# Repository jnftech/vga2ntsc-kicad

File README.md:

# RetroTINK VGA2NTSC - KiCad Conversion/Modification

This is a modified version of Mike Chi's VGA2NTSC v1.1.
The first goal was to convert the original Altium source files to KiCad - a free and open source tool - as not everyone has access to Altium. Secondly, most footprints have been swapped to make the board more DIY friendly - for example swapping 0402 components (difficult to solder by hand) with 0805 or larger.

As of April 2023, the version shown here is a "final" version (meaning I will no longer make further improvements) that I completed in mid-2021 and only now finally publishing to Github. The changes between the Old version (2020/04/20, archived in the "_Old" folder) and this version are outlined below. 

### Goals:
- Convert original Altium project to KiCad
- Use 0805 footprints instead of smaller packages
- Keep location of jacks and mounting holes in the same locations
- Keep circuit identical to original schematics
- Adjust vertical board size slightly to fit within 100x100mm size limit for cheap boards with many popular PCB fabs
- Add a footprint for a DC barrel jack instead of USB power (either-or can be used in the same spot). Warning has been added to the board denoting 5V power only
- Modified power distribution rail using bottom layer of board
- Relocated clock section to minimize routing near other signals or underneath video amp
- Minimized the use of vias for signal traces where possible.
- More KiCad practice for me
- Finally try to publish something on GitHub (first repo!)

### Changed from 2020/04/20 version:
- Tided up board outline and removed some workaround circular holes in some footprints.
- Added selectable HV/CSYNC switch
- AC coupling on the RGB lines of Scart Output (C22 - C25). The original design left these DC coupled. DC coupling can still be achieved by simply jumping the capacitor pads (for example using larger 0 ohm resistors, like 1206 or 1812)
- There are a few extra "tinkerer/advanced" pins (see below) but there are two solder jumpers implemented to make use of these.

### TL;DR on the two solder jumpers (JP1 and JP2)
- Close these both with solder if you want just NTSC video output. If you are not sure, then just close them both.

### Advanced/Tinkerer features (ignore this if you want just NTSC output with the standard board setup)
- Added a way to bypass the on-board clock circuit. This might be handy for someone wanting to get PAL output from the board by feeding in an external clock signal (EXT_CLOCK). See warning note below.
  - Note that JP1 must be closed with solder for "normal" NTSC operation using the onboard clock circuit. Leave JP1 open to feed external clock signal.
- Added pads for manipulating the NTSC/PAL pin on the AD725 if desired. Switching to PAL would require a different clock signal (see above, and see warning note below).
  - Close JP2 with solder for "normal" NTSC operation. (Just pulls the AD's STND pin high)
  - Leave JP2 open if you want the ability to toggle the mode.
  - WARNING: The three pins in the middle of the board (labeled "NTSC", "", and "PAL" on the underside) are there to implement a toggle. However the "NTSC" and "PAL" pins are just VCC and GND respectively, with the center pin being connected to the AD725's STND pin (which must be pulled either HIGH for NTSC, or LOW for PAL). As I did not have the foresight to think that through, there are no pullup/pulldown resistors. In other words DO NOT SHORT THE NTSC AND PAL PINS TOGETHER, and dont use MBB-style switches to toggle between.
- Added a YTRAP pad for feeding an external YTRAP circuit to the AD725.

### Notes:

<span style="color: red;">This board and circuit, as depicted in this repository, will only deliver an NTSC signal (hence the name VGA2NTSC).
Presence of the aforementioned extra pins (jumpers, clock and NTSC/PAL pins) do not indicate that this board natively supports PAL or any standard other than NTSC.
Those options are for advanced users/tinkerers that are prepard to supply the appropriate clock signal to the board to support other standards.</span>

The board design uses vias-in-pads. This can be a problem for some fabs. JLCPCB (at least with default HASL plating) and OSHpark dont seem to have an issue with this, but some fabs might depending on how they plate the pads. You may need to adjust the locations of the vias and add a couple traces to compensate, should you run into this situation.

### Tools used for conversion:
- Altium2Kicad https://github.com/thesourcerer8/altium2kicad
- Tracespace View (conversion of original Gerbers to SVG for reference and silkscreen adaptations - Alitum2Kicad doesn’t translate original fonts/graphics) https://tracespace.io/view/
- KiCad 5.1.8 https://www.kicad.org/
- Inkscape https://inkscape.org/

<p align="center">
<br />

<br />
</p>

This derivative work maintains the same source license as the original board.
https://www.retrotink.com/post/vga2ntsc-released

### “Mike Chi” License:
(From https://www.retrotink.com/post/vga2ntsc-released)

```
License
The materials are released under the terms below. I don't have time for pedantic nonsense or legal theory and like to keep things simple. I call this the 'Mike Chi' license.

- For each project, at my sole discretion, I may release whatever sources, to whatever level of abstraction, that I deem appropriate. Additional information/materials may be released on a scheduled determined at my sole discretion.
- You may modify, use or adapt any or all portions of the released material for any purpose you wish, including sale.
- The exception is that the files may not be used for commercial activities by entities, determined at my sole discretion, that have a history of violating intellectual property rights or licenses.
- If these materials were helpful and/or of use to you, I only ask that you provide some form of acknowledgment that you feel is fair.
- I'd also love to hear about how you're using it!
- If you re-distribute the material in a substantially unaltered form, please include this notice.
- NO WARRANTY EXPRESSED OR IMPLIED. WE TAKE ABSOLUTELY NO RESPONSIBILITY FOR WHAT MAY OCCUR FROM USAGE OF THE FILES.
- WE CANNOT AND WILL NOT OFFER ANY SUPPORT FOR THE USAGE OF THE FILES. IF YOU DO NOT AGREE WITH THESE TERMS THEN DO NOT USE ANY OF THE MATERIALS AND DON'T COMPLAIN.
```

https://www.retrotink.com/

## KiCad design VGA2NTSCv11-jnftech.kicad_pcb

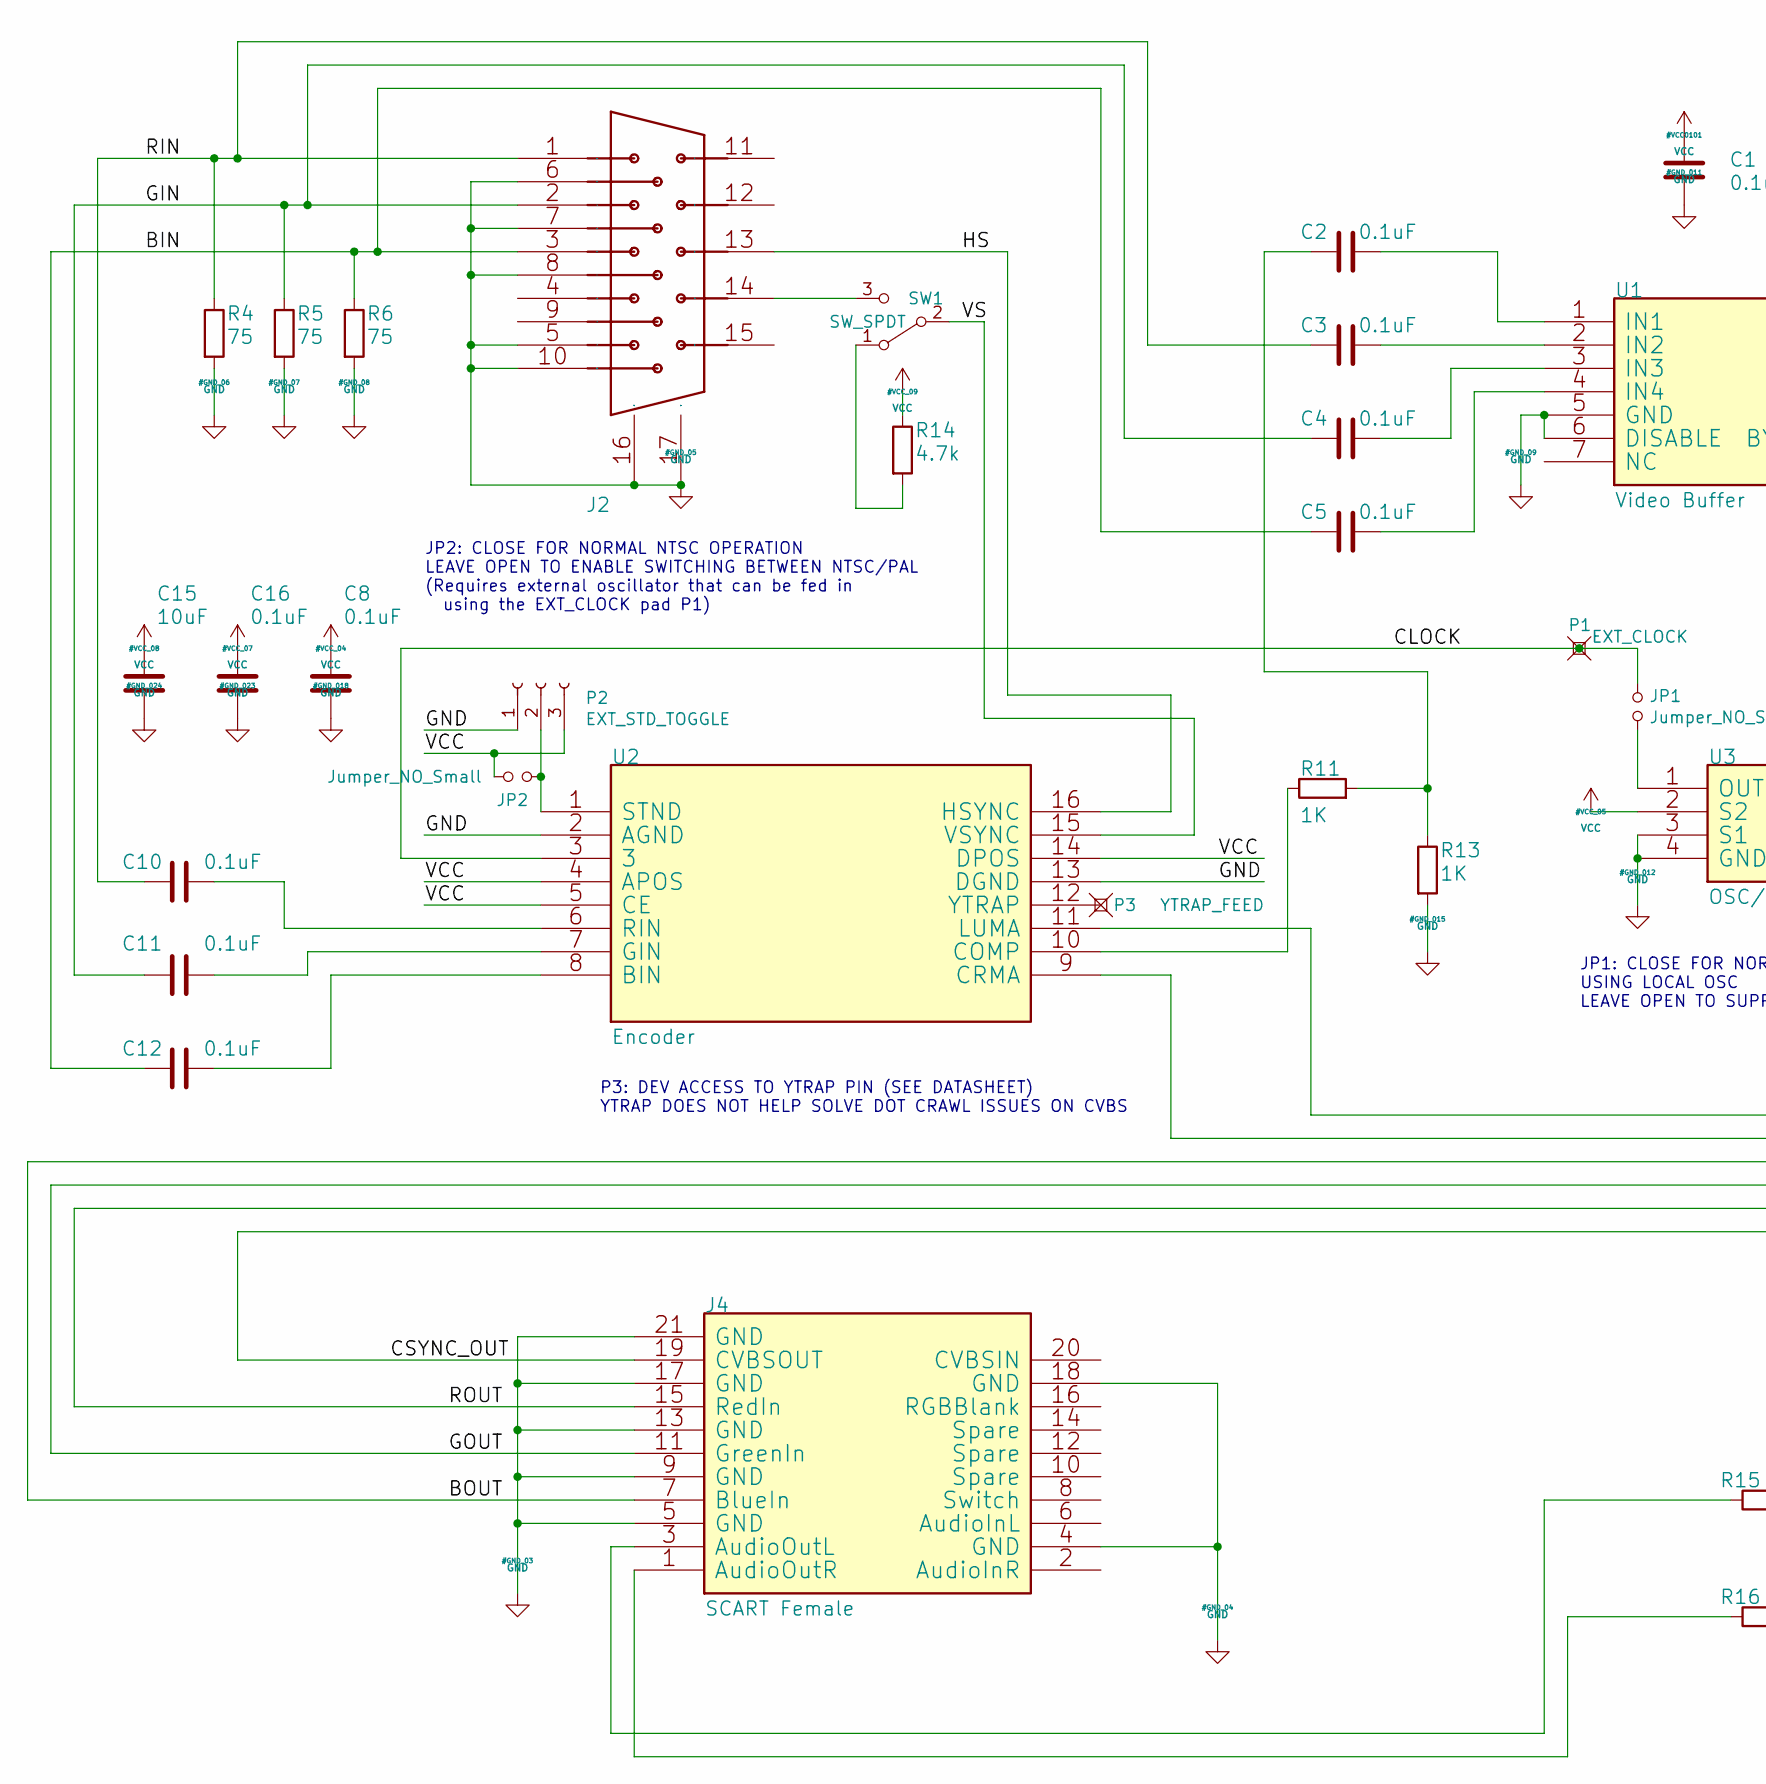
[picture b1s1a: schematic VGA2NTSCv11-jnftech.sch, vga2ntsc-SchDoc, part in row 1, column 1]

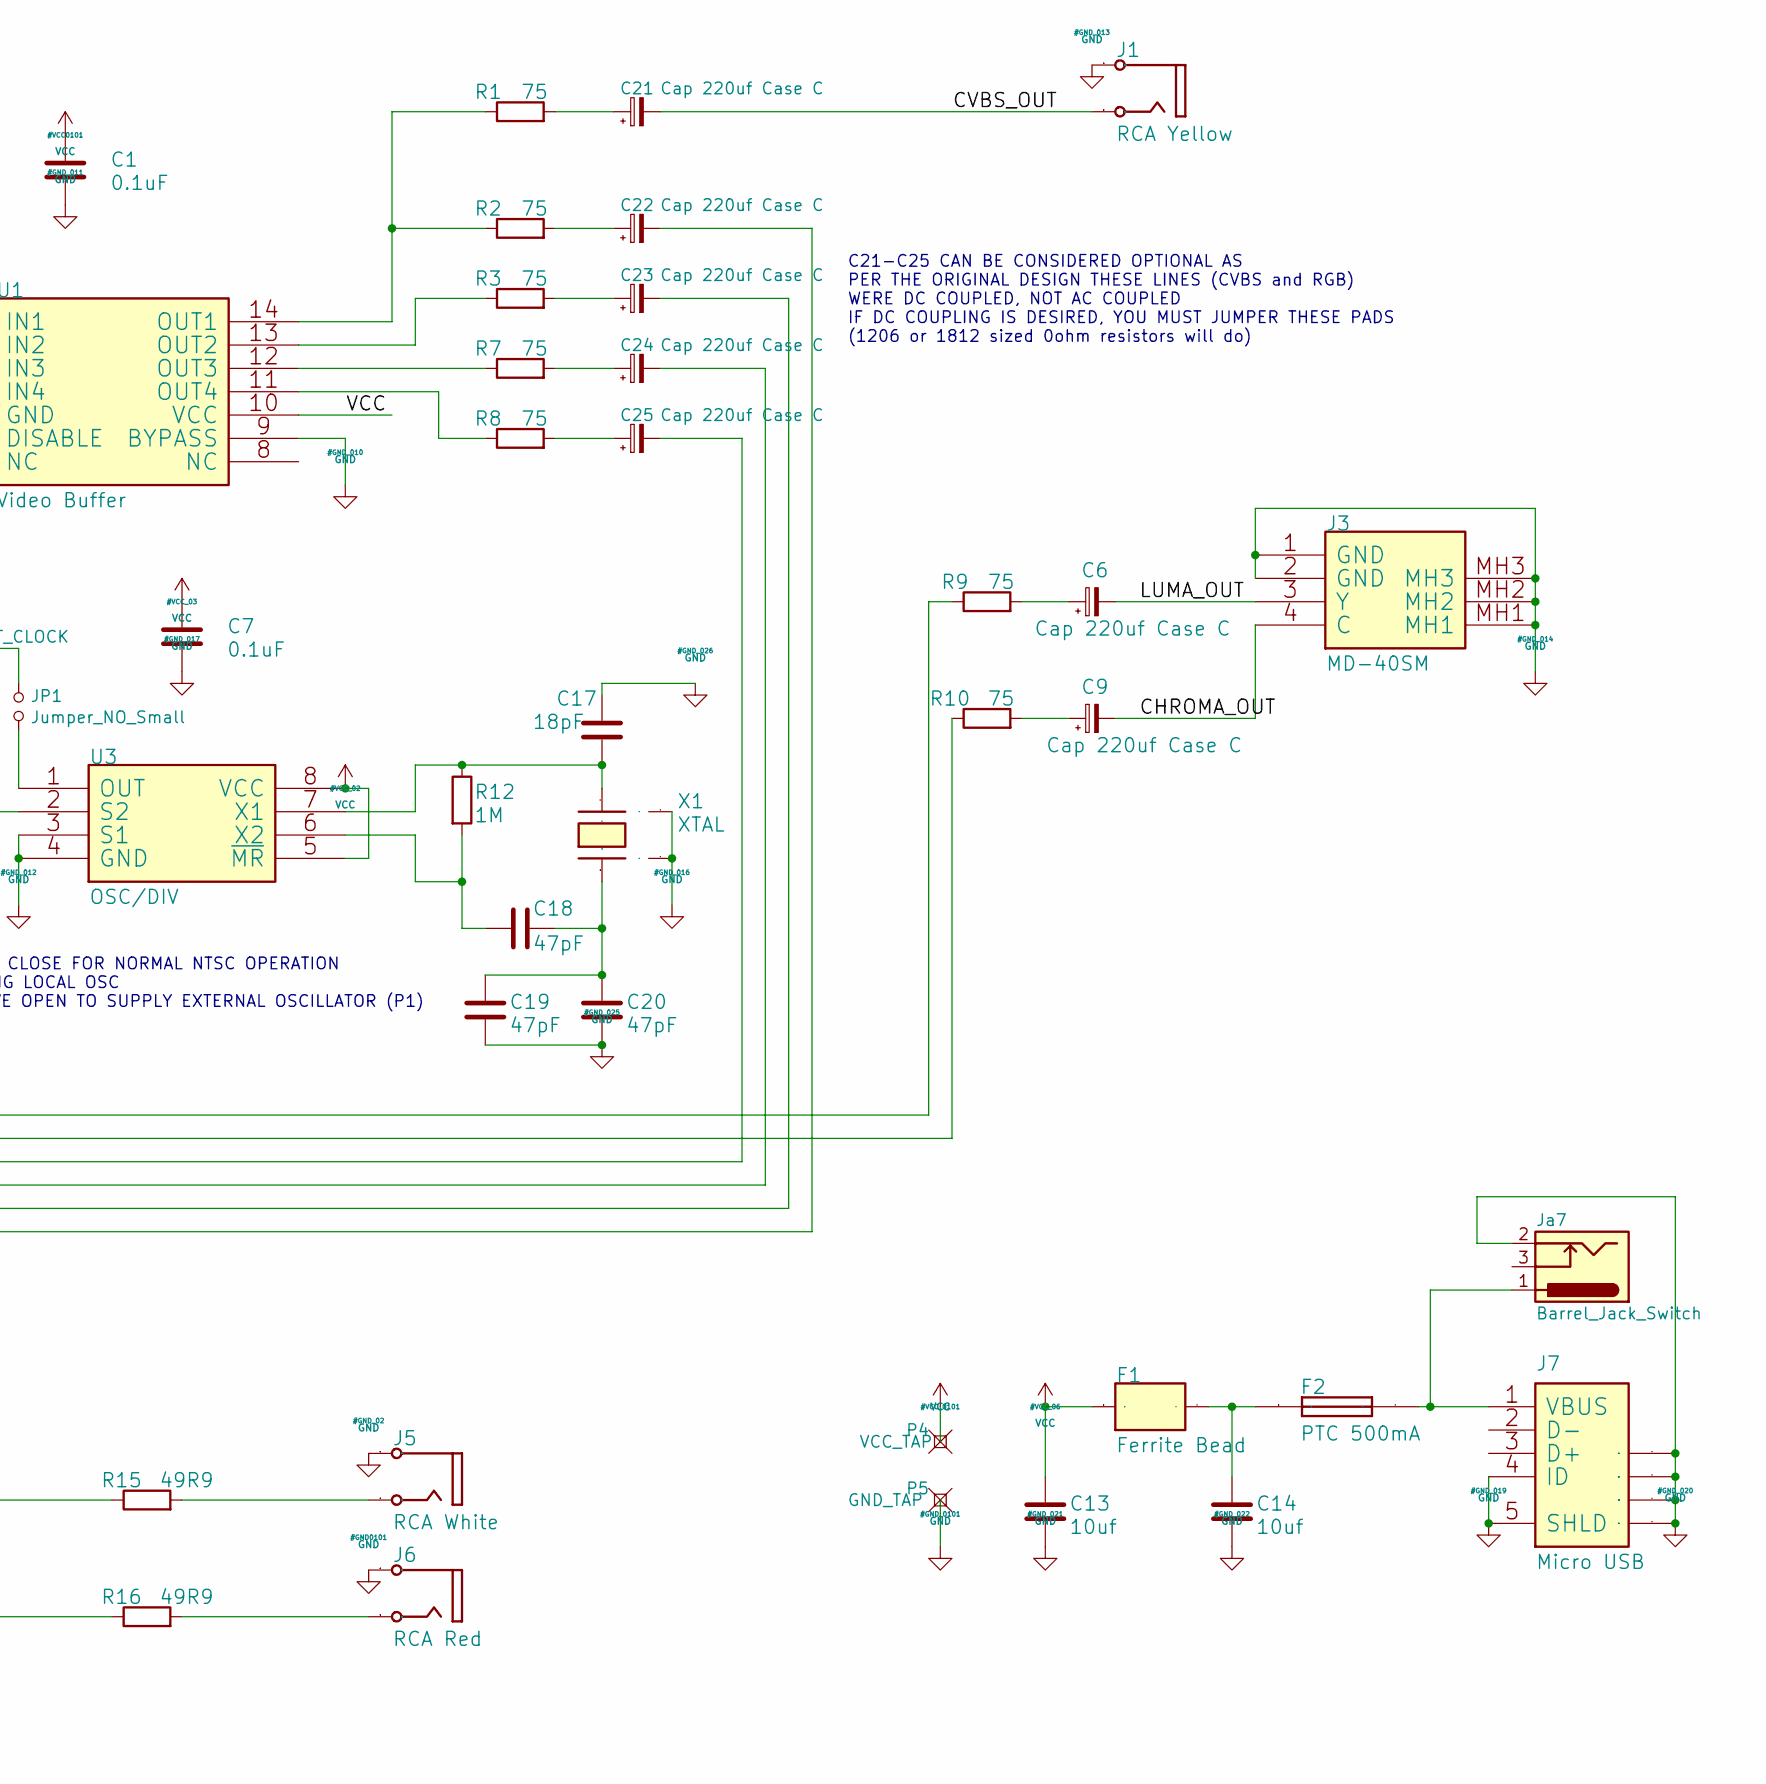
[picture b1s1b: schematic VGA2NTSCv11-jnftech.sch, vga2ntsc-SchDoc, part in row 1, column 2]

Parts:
C1, C2, C3, C4, C5, C7, C8, C10, C11, C12, C16: 0.1uF; R_0805_1mm
C6, C9, C21, C22, C23, C24, C25: Cap 220uf Case C; CP_Tantalum_Case-C_EIA-6032-28_JFT
C13, C14: 10uf; R_0805_1mm
C15: 10uF; R_0805_1mm
C17: 18pF; R_0805_1mm
C18, C19, C20: 47pF; R_0805_1mm
F1: Ferrite Bead; R_0805_1mm
F2: PTC 500mA; R_1812_1206-JFT
J1: RCA Yellow; RCJ-04x_NoHole
J2: AMPHENOL_L77HDE15SD1CH4F_Drill1SizeOval
J3: MD-40SM; CUI_MD-40SM_VGA2NTSC
J4: SCART Female; SCART-F-RA-NoHole
J5: RCA White; RCJ-04x_NoHole
J6: RCA Red; RCJ-04x_NoHole
J7: Micro USB; Connector_MicroUSB_Amp10118194-0001LF
JP1, JP2: Jumper_NO_Small; WirepadJumperSm
Ja7: Barrel_Jack_Switch; BARREL_JACK-JFT
P1: EXT_CLOCK; TH_Hole_One_1mm
P2: EXT_STD_TOGGLE; Pin_Header_Straight_1x03_Pitch2.54mm_NoSilk
P3: YTRAP_FEED; TH_Hole_One_1mm
P4: VCC_TAP; TH_Hole_One_1mm
P5: GND_TAP; TH_Hole_One_1mm
R1, R2, R3, R7, R8, R9, R10: 75; R_0805_1mm
R4, R5, R6: 75; R_0805_1mm; Tolerance 1%
R11, R13: 1K; R_0805_1mm; Tolerance 1%
R12: 1M; R_0805_1mm; Tolerance 1%
R14: 4.7k; R_0805_1mm; Tolerance 5%
R15, R16: 49R9; R_0805_1mm
SW1: SW_SPDT; SW_HRO-SK-12D02_SPDT_Angled
U1: Video Buffer; TSSOP-14_4.4x5mm_Pitch0.65mm-JFT
U2: Encoder; SOIC-16W_7.5x10.3mm_Pitch1.27mm_HS
U3: OSC/DIV; SOIC-8_3.9x4.9mm_Pitch1.27mm-JFT
X1: XTAL; Crystal_4SMD-NL_3.2mmx2.5mm_HandSolder

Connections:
/BIN: C5.1, C12.1, J2.3, R6.1
/BOUT: C25.2, J4.7 (BlueIn)
/CHROMA_OUT: C9.2, J3.4 (C)
/CLOCK: JP1.1, P1.1, U2.3
/CSYNC_OUT: C22.2, J4.19 (CVBSOUT)
/CVBS_OUT: C21.2, J1.2B (Signal)
/GIN: C4.1, C11.1, J2.2, R5.1
/GOUT: C24.2, J4.11 (GreenIn)
/HS: J2.13, U2.16 (HSYNC)
/LUMA_OUT: C6.2, J3.3 (Y)
/RIN: C3.1, C10.1, J2.1, R4.1
/ROUT: C23.2, J4.15 (RedIn)
/VS: SW1.2 (B), U2.15 (VSYNC)
GND: C1.1, C7.1, C8.1, C13.2, C14.2, C15.2, C16.1, C17.1, C19.1, C20.1, J1.1A (Ground), J2.5, J2.6, J2.7, J2.8, J2.10, J2.16, J2.17, J3.1 (GND), J3.2 (GND), J3.MH1, J3.MH2, J3.MH3, J4.4 (GND), J4.5 (GND), J4.9 (GND), J4.13 (GND), J4.17 (GND), J4.18 (GND), J4.21 (GND), J5.1A (Ground), J6.1A (Ground), J7.4 (ID), J7.5 (SHLD), J7.6 (SHLD), J7.7 (SHLD), J7.8 (SHLD), J7.9 (SHLD), Ja7.2, P2.1, P5.1, R4.2, R5.2, R6.2, R13.2, U1.5 (GND), U1.6 (DISABLE), U1.9 (BYPASS), U2.2 (AGND), U2.13 (DGND), U3.3 (S1), U3.4 (GND), X1.2, X1.4
unnamed: C2.1, R11.2, R13.1
unnamed: C2.2, U1.1 (IN1)
unnamed: C3.2, U1.2 (IN2)
unnamed: C4.2, U1.3 (IN3)
unnamed: C5.2, U1.4 (IN4)
unnamed: C6.1, R9.2
unnamed: C9.1, R10.2
unnamed: C10.2, U2.6 (RIN)
unnamed: C11.2, U2.7 (GIN)
unnamed: C12.2, U2.8 (BIN)
unnamed: C14.1, F1.2, F2.1
unnamed: C17.2, R12.1, U3.7 (X1), X1.3
unnamed: C18.1, R12.2, U3.6 (X2)
unnamed: C18.2, C19.2, C20.2, X1.1
unnamed: C21.1, R1.2
unnamed: C22.1, R2.2
unnamed: C23.1, R3.2
unnamed: C24.1, R7.2
unnamed: C25.1, R8.2
unnamed: F2.2, J7.1 (VBUS), Ja7.1
unnamed: J2.14, SW1.3 (C)
unnamed: J4.1 (AudioOutR), R16.1
unnamed: J4.3 (AudioOutL), R15.1
unnamed: J5.2B (Signal), R15.2
unnamed: J6.2B (Signal), R16.2
unnamed: JP1.2, U3.1 (OUT)
unnamed: JP2.1, P2.2, U2.1 (STND)
unnamed: P3.1, U2.12 (YTRAP)
unnamed: R1.1, R2.1, U1.14 (OUT1)
unnamed: R3.1, U1.13 (OUT2)
unnamed: R7.1, U1.12 (OUT3)
unnamed: R8.1, U1.11 (OUT4)
unnamed: R9.1, U2.11 (LUMA)
unnamed: R10.1, U2.9 (CRMA)
unnamed: R11.1, U2.10 (COMP)
unnamed: R14.2, SW1.1 (A)
VCC: C1.2, C7.2, C8.2, C13.1, C15.1, C16.2, F1.1, JP2.2, P2.3, P4.1, R14.1, U1.10 (VCC), U2.4 (APOS), U2.5 (CE), U2.14 (DPOS), U3.2 (S2), U3.5 (~MR), U3.8 (VCC)

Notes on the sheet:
JP1: CLOSE FOR NORMAL NTSC OPERATION USING LOCAL OSC LEAVE OPEN TO SUPPLY EXTERNAL OSCILLATOR (P1)
JP2: CLOSE FOR NORMAL NTSC OPERATION LEAVE OPEN TO ENABLE SWITCHING BETWEEN NTSC/PAL (Requires external oscillator that can be fed in using the EXT_CLOCK pad P1)
C21-C25 CAN BE CONSIDERED OPTIONAL AS PER THE ORIGINAL DESIGN THESE LINES (CVBS and RGB) WERE DC COUPLED, NOT AC COUPLED IF DC COUPLING IS DESIRED, YOU MUST JUMPER THESE PADS (1206 or 1812 sized 0ohm resistors will do)
P3: DEV ACCESS TO YTRAP PIN (SEE DATASHEET) YTRAP DOES NOT HELP SOLVE DOT CRAWL ISSUES ON CVBS

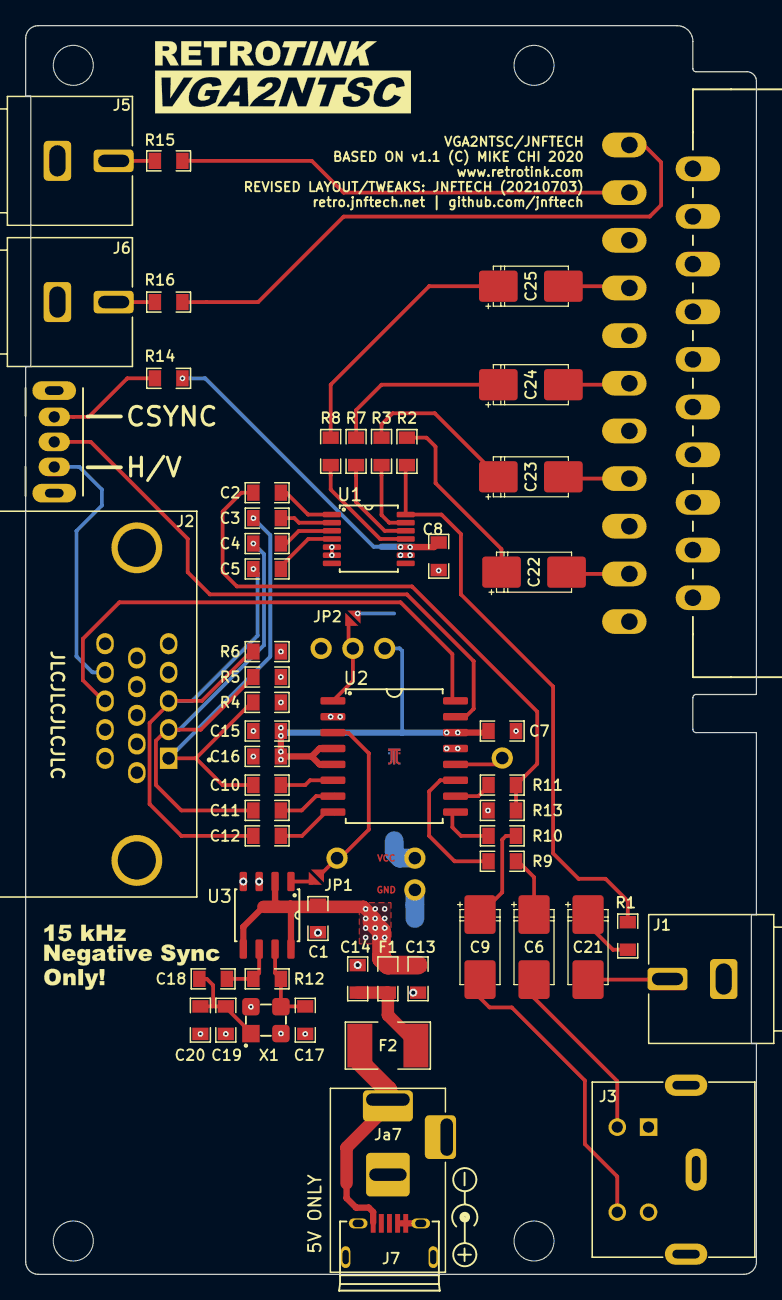
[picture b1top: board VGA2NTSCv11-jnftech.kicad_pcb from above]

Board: 2 copper layers, 58.4 x 99.8 mm, 63 parts (0 on the bottom side), 51 nets.

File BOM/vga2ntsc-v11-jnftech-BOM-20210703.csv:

Designator,ManufacturerPartNumber,DigiKey,LCSC,Quantity,Value,Size,Voltage,Tolerance,Comments,Substitute
"C1, C2, C3, C4, C5, C7, C8, C10, C11, C12, C16",CL21B104JBCNNNC,1276-1090-1-ND,C62912,11,100nf,0805,>=16v,5%,Ceramic Cap X7R,
"C6, C9, C21, C22, C23, C24, C25",TAJC227M006RNJ,478-11057-1-ND,C132271,7,220uf,CASE-C,6.3V,10%,Tantalum Cap,Any Case C 220uf =>6.3v
"C13, C14, C15",GRM21BR61C106KE15K,490-6473-1-ND,C408141,3,10uf,0805,10v,10%,X5R,CL21A106KOQNNNE
C17,CL21C180JBANNNC,1276-1107-1-ND,C170109,1,18pf,0805,50v,5%,C0G,
"C18, C19, C20",CL21C470JBANNNC,1276-1156-1-ND,C14857,3,47PF,0805,50V,5%,C0G,
F1,BLM21PG221SN1D,490-1054-1-ND,C85840,1,100mOhm,0805,2A,220R @100Mhz,Ferrite Bead,
F2,1812L050/30,F4159CT-ND,C151168,1,1A,1812,30V,,Fuse,
J1,RCJ-044,CP-1421-ND,N/A,1,,,,,RCA Jack Yellow,
J2,ICD15S13E4GX00LF,609-5181-ND,C75754,1,,,,,VGA Dsub,(LCSC) DS1038-15FBNSiA74-0CC
J3,MD-40SM,CP-2240-ND,N/A,1,,,,,S-Video,
J4,SCART,Find it on Aliexpress?,N/A,1,,,,,SCART Female,
J7,10118194-0001LF,609-4618-1-ND,C132563,1,,,,,USB Connector,
J7 (Alternate),PJ-002A,CP-002A-ND,C319099,1,,,,,DC Barrel (Use instead of USB Power input if desired),(LCSC) XKB DC-005-2.5A-2.0
J5,RCJ-043,CP-1420-ND,N/A,1,,,,,RCA Jack White,
J6,RCJ-042,CP-1419-ND,N/A,1,,,,,RCA Jack Red,
"R1, R2, R3, R4, R5, R6, R7, R8, R9, R10",RC0805FR-0775RL,311-75.0CRCT-ND,C141697,10,75R,0805,,1%,Resistor,
"R11, R13",RC0805FR-071KL,311-1.00KCRCT-ND,C95781,2,1K,0805,,1%,Resistor,
R12,RC0805FR-071ML,311-1.00MCRCT-ND,C107700,1,1M,0805,,1%,Resistor,
R14,RC0805FR-074K7L,311-4.70KCRCT-ND,C60816,1,4K7,0805,,1%,Resistor,
"R15, R16",RC0805FR-0749R9L,311-49.9CRCT-ND,C132320,2,49R9,0805,,1%,Resistor,
SW1,OS102011MA1QS1,CKN9560-ND,C136722,1,,,,,CSYNC/HV Switch,(LCSC) HROparts SK-12D02-VG5
U1,THS7373IPWR,296-25626-1-ND,N/A,1,,,,,Video Amp,
U2,AD725ARZ,AD725ARZ-ND,N/A,1,,,,,Video Encoder,
U3,"74HC6323AD,112",1727-3330-ND,N/A,1,,,,,Binary Counter (Clock),
X1,ABM8-28.63636MHZ-B2-T,535-9143-1-ND,N/A,1,,,,,Oscillator,

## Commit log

2020-04-21 Fixed filename of rescue.lib
2020-04-21 Cleanup associations between schematic, PCB, and Netlist
2020-04-22 Fix Polarity silkscreen
2020-05-06 Fix silkscreen errors
2021-11-10 Update README.md
    https://forum.kicad.info/t/warning-avoid-all-links-to-kicad-pcb-org-use-kicad-org/31521
2023-04-29 Updating project to 20210703 version
2023-04-29 Fixed typo
2023-04-29 Quick updates or redundant text fixes
2023-04-29 Publish BOM
2025-05-04 Update README.md
    Clarifying PAL support and rewording the tinkerer/advanced pin descriptions
